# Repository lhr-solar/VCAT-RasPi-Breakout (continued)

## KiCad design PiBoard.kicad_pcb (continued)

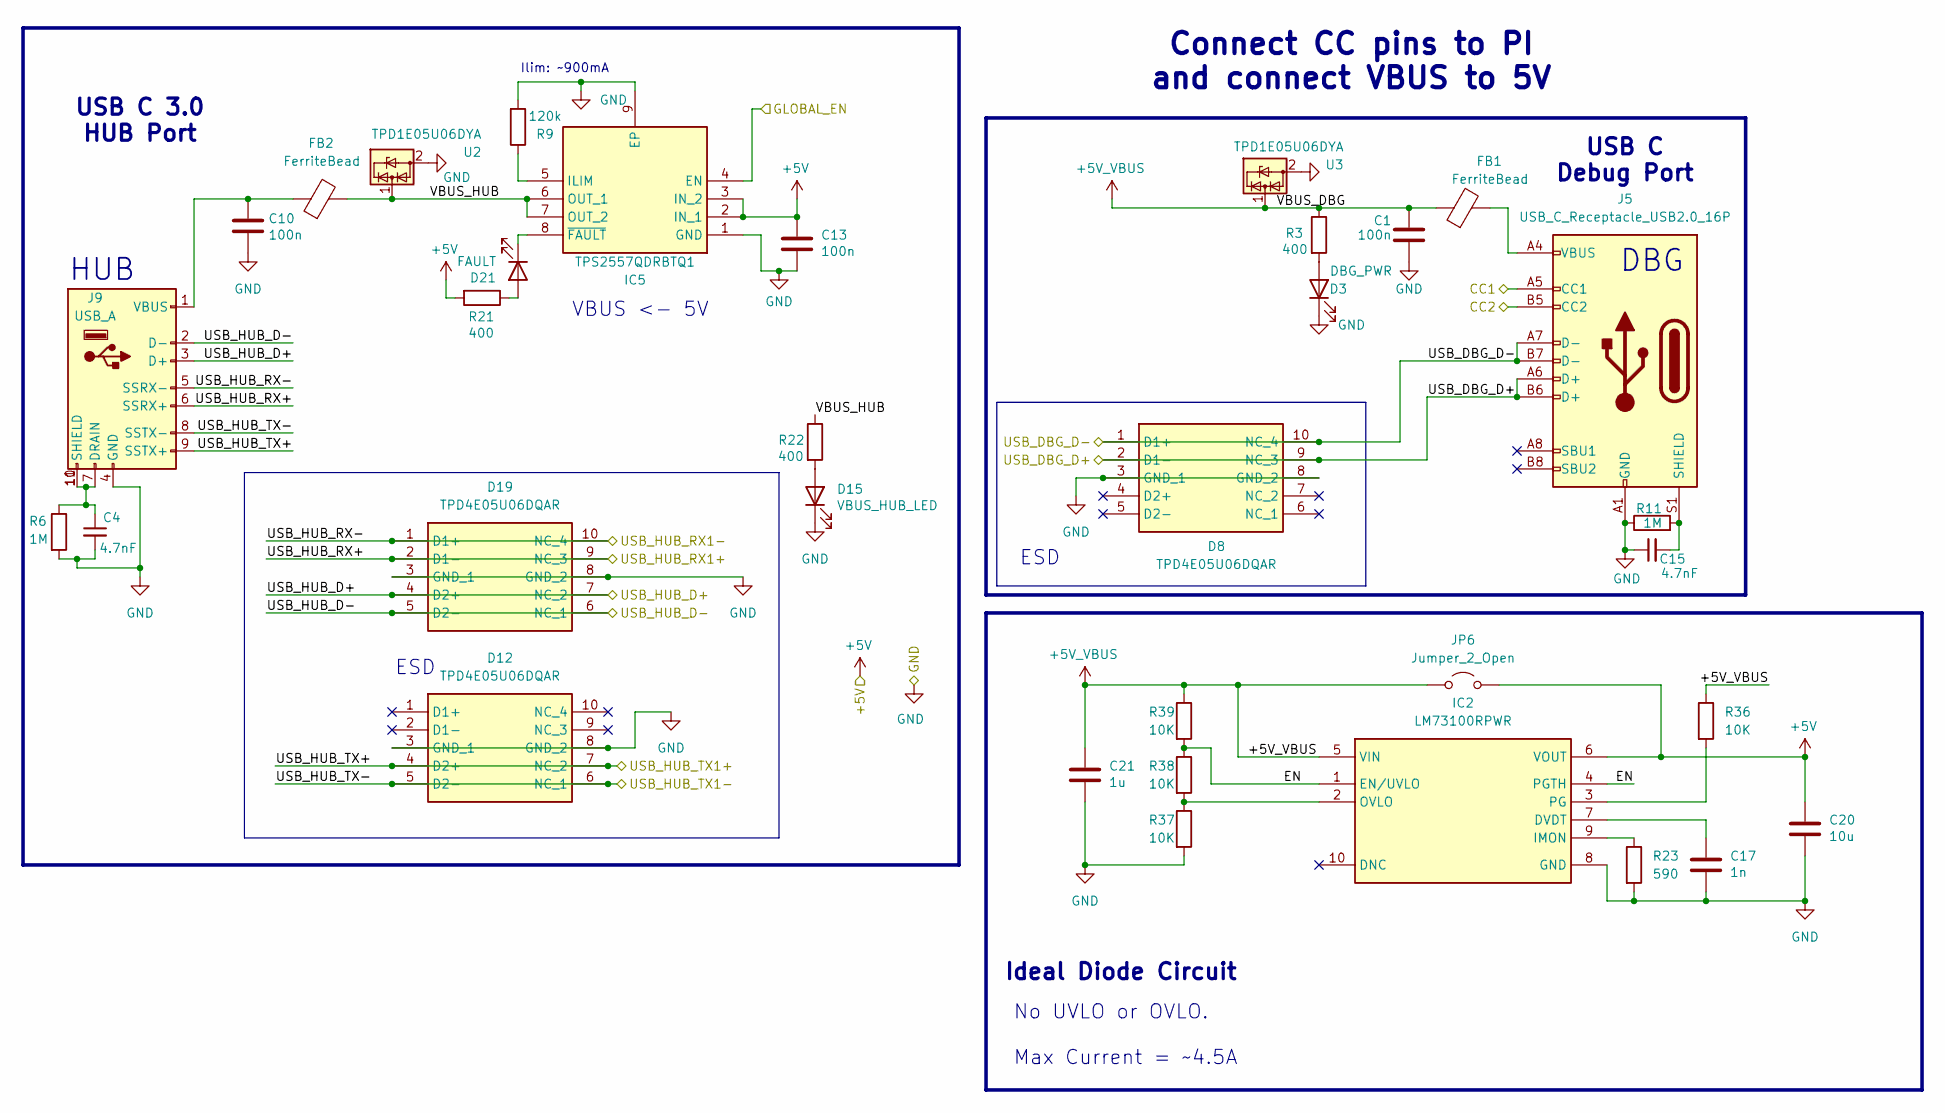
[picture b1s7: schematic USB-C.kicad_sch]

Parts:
C1, C10, C13: 100n; C_0603_1608Metric_Pad1.08x0.95mm_HandSolder; JLC C14663
C4, C15: 4.7nF; C_0603_1608Metric_Pad1.08x0.95mm_HandSolder; JLC C696859
C17: 1n; C_0603_1608Metric_Pad1.08x0.95mm_HandSolder; JLC C1588
C20: 10u; C_0805_2012Metric_Pad1.18x1.45mm_HandSolder; JLC C440198
C21: 1u; C_0603_1608Metric_Pad1.08x0.95mm_HandSolder; JLC C15849
D3: DBG_PWR; LED_0603_1608Metric_Pad1.05x0.95mm_HandSolder; JLC C2289
D8, D12, D19: TPD4E05U06DQAR; IC_TPD4E05U06QDQARQ1; JLC C138714
D15: VBUS_HUB_LED; LED_0603_1608Metric_Pad1.05x0.95mm_HandSolder; JLC C2289
D21: FAULT; LED_0603_1608Metric_Pad1.05x0.95mm_HandSolder; JLC C2286
FB1, FB2: FerriteBead; L_0805_2012Metric_Pad1.05x1.20mm_HandSolder; JLC C1015
IC2: LM73100RPWR; Mouser Part Number 595-LM73100RPWR
IC5: TPS2557QDRBTQ1; SON65P300X300X100-9N-D; Mouser Part Number 595-TPS2557QDRBTQ1
J5: USB_C_Receptacle_USB2.0_16P; USB_C_Receptacle_GCT_USB4105-xx-A_16P_TopMnt_Horizontal; JLC C37616412
J9: USB_A; CONN_484050003_MOL; JLC C565032
JP6: Jumper_2_Open; PinHeader_1x02_P2.54mm_Vertical; JLC N/A
R3, R21, R22: 400; R_0603_1608Metric_Pad0.98x0.95mm_HandSolder; JLC C5841024
R6, R11: 1M; R_0603_1608Metric_Pad0.98x0.95mm_HandSolder; JLC C22935
R9: 120k; R_0603_1608Metric_Pad0.98x0.95mm_HandSolder; JLC C25808
R23: 590; R_0603_1608Metric_Pad0.98x0.95mm_HandSolder; JLC C2076662
R36: 10K; R_0603_1608Metric_Pad0.98x0.95mm_HandSolder; JLC C25804
R37, R38, R39: 10K; R_0603_1608Metric_Pad0.98x0.95mm_HandSolder
U2, U3: TPD1E05U06DYA; D_SOD-523; JLC TPD1E05U06DYAR

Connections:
+5V: C13.1, C20.1, IC2.6 (VOUT), IC5.2 (IN_1), IC5.3 (IN_2), JP6.2 (B), R21.2; also elsewhere on the board
+5V_VBUS: C1.1, C21.1, FB1.1, IC2.5 (VIN), JP6.1 (A), R3.1, R36.1, R39.1, U3.1 (I/O)
/CM5 GPIO/CC1: J5.A5 (CC1); also elsewhere on the board
/CM5 GPIO/CC2: J5.B5 (CC2); also elsewhere on the board
/CM5 GPIO/GLOBAL_EN: IC5.4 (EN); also elsewhere on the board
/High Speed/USB-C/EN: IC2.1 (EN/UVLO), IC2.4 (PGTH), R38.1, R39.2
/High Speed/USB-C/VBUS_HUB: FB2.2, IC5.6 (OUT_1), IC5.7 (OUT_2), R22.1, U2.1 (I/O)
/High Speed/USB_DBG_D+: D8.2 (D1-), D8.9 (NC_3), J5.A6 (D+), J5.B6 (D+); also elsewhere on the board
/High Speed/USB_DBG_D-: D8.1 (D1+), D8.10 (NC_4), J5.A7 (D-), J5.B7 (D-); also elsewhere on the board
/High Speed/USB_HUB_D+: D19.4 (D2+), D19.7 (NC_2), J9.3 (D+); also elsewhere on the board
/High Speed/USB_HUB_D-: D19.5 (D2-), D19.6 (NC_1), J9.2 (D-); also elsewhere on the board
/High Speed/USB_HUB_RX1+: D19.2 (D1-), D19.9 (NC_3), J9.6 (SSRX+); also elsewhere on the board
/High Speed/USB_HUB_RX1-: D19.1 (D1+), D19.10 (NC_4), J9.5 (SSRX-); also elsewhere on the board
/High Speed/USB_HUB_TX1+: D12.4 (D2+), D12.7 (NC_2), J9.9 (SSTX+); also elsewhere on the board
/High Speed/USB_HUB_TX1-: D12.5 (D2-), D12.6 (NC_1), J9.8 (SSTX-); also elsewhere on the board
GND: C1.2, C4.2, C10.2, C13.2, C15.1, C17.2, C20.2, C21.2, D3.1 (K), D8.3 (GND_1), D8.8 (GND_2), D12.3 (GND_1), D12.8 (GND_2), D15.1 (K), D19.3 (GND_1), D19.8 (GND_2), IC2.8 (GND), IC5.1 (GND), IC5.9 (EP), J5.A1 (GND), J5.A12 (GND), J5.B1 (GND), J5.B12 (GND), J9.4 (GND), R6.2, R9.2, R11.1, R23.2, R37.2, U2.2 (GND), U3.2 (GND); also elsewhere on the board
unnamed: D3.2 (A), R3.2
unnamed: D15.2 (A), R22.2
unnamed: D21.2 (A), R21.1
unnamed: D21.1 (K), IC5.8 (~FAULT)
unnamed: FB1.2, J5.A4 (VBUS), J5.A9 (VBUS), J5.B4 (VBUS), J5.B9 (VBUS)
unnamed: C17.1, IC2.7 (DVDT)
unnamed: IC2.9 (IMON), R23.1
unnamed: IC2.2 (OVLO), R37.1, R38.2
unnamed: IC2.3 (PG), R36.2
unnamed: IC5.5 (ILIM), R9.1
unnamed: C15.2, J5.S1 (SHIELD), R11.2
unnamed: C4.1, J9.7 (DRAIN), J9.10 (SHIELD), J9.11 (SHIELD), R6.1
unnamed: C10.1, FB2.1, J9.1 (VBUS)

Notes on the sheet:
Ideal Diode Circuit
Ilim: ~900mA
DBG
ESD
No UVLO or OVLO. Max Current = ~4.5A
HUB
Connect CC pins to PI and connect VBUS to 5V
VBUS <- 5V
USB C 3.0 HUB Port
USB C Debug Port

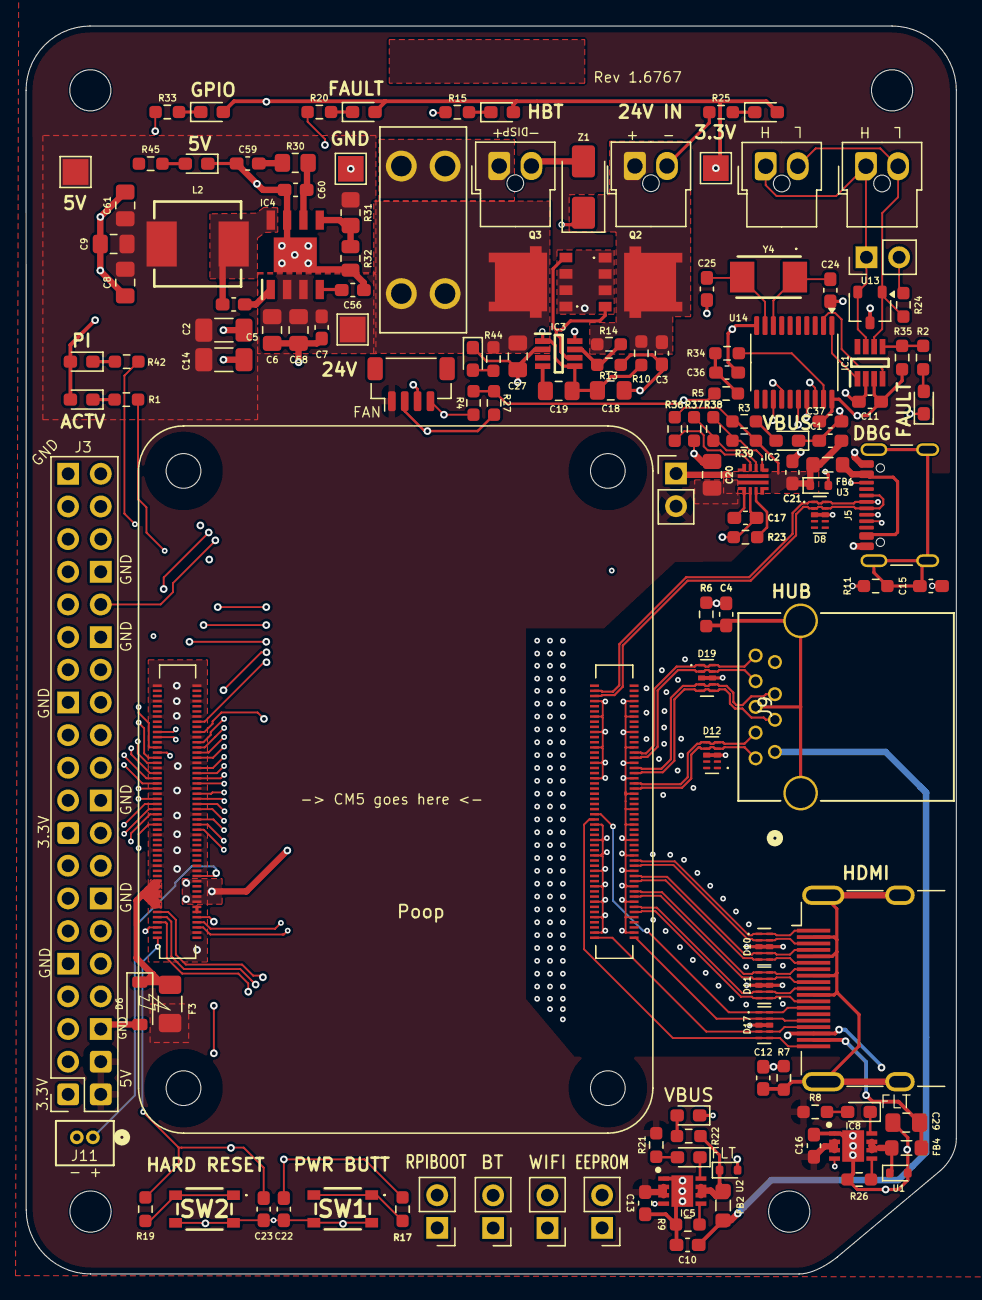
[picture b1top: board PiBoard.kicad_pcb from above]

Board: 4 copper layers, 72.3 x 97.1 mm, 139 parts (0 on the bottom side), 123 nets.

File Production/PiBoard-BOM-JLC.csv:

"Reference","Value","Footprint","Qty","JLC"
"U1,U2,U3","TPD1E05U06DYA","Diode_SMD:D_SOD-523","3","TPD1E05U06DYAR"
"BT2,H1,H2,H3,H4,IC3,J1,J2,J3,J6,J8,J11,J12,J14,JP1,JP2,JP3,JP4,JP5,JP6,TP1,TP2,TP3,TP5","Battery_Cell,CarCANConnector,CarLVPowerConnector,Display Breakout,Fan Header,Jumper_2_Open,LM74502HDDFR,MountingHole,RPI Pin-Header,RTC Battery Conn,RTC Battery Port,TestPoint","Connector_JST:JST_SH_BM04B-SRSS-TB_1x04-1MP_P1.00mm_Vertical,Connector_PinHeader_2.54mm:PinHeader_1x02_P2.54mm_Vertical,Connector_PinSocket_2.54mm:PinSocket_2x20_P2.54mm_Vertical,Controls_Pi:CONN02_530470210_MOL,MountingHole:MountingHole_3.2mm_M3,TestPoint:TestPoint_Pad_2.0x2.0mm,UTSVT_Connectors:Molex_Nano-Fit_105309-xx02_1x02_P2.50mm_Vertical,UTSVT_Power_SP:SOT65P280X110-8N","24","N/A"
"Q2,Q3","NVMFWS1D7N04XMT1G","Controls_Pi:NVMFWS3D0P04M8LT1G","2","C52190853"
"F3","RFuse","Fuse:Fuse_1206_3216Metric_Pad1.42x1.75mm_HandSolder","1","C42449089"
"J5","USB_C_Receptacle_USB2.0_16P","UTSVT_Connectors:USB_C_Receptacle_GCT_USB4105-xx-A_16P_TopMnt_Horizontal","1","C37616412"
"R26","180k","Resistor_SMD:R_0603_1608Metric_Pad0.98x0.95mm_HandSolder","1","C22356446"
"D6","PTVS6V0S1UR","Diode_SMD:D_SOD-123","1"," C18723426"
"C2,C14","100uF","Capacitor_SMD:C_1206_3216Metric_Pad1.33x1.80mm_HandSolder","2","C7432784"
"Z1","SMAF4759A-TP","Diode_SMD:D_SMA","1","C7083101"
"Module2","ComputeModule5-CM5","CM5IO:Raspberry-Pi-5-Compute-Module","1","C6782225"
"R3,R8,R21,R22,R45","400","Resistor_SMD:R_0603_1608Metric_Pad0.98x0.95mm_HandSolder","5","C5841024"
"L2","4.7uH","Controls_Pi:INDPM110100X540N","1","C5189748"
"U13","CDSOT23-T24CAN","Package_TO_SOT_SMD:SOT-23W","1","C2959841"
"R31","53.6k","Resistor_SMD:R_0805_2012Metric_Pad1.20x1.40mm_HandSolder","1","C2930115"
"SW1,SW2","SW_Push","CM5IO:TL3365AF180QG","2","C2886926"
"IC5,IC8","TPS2557QDRBTQ1","Controls_Pi:SON65P300X300X100-9N-D","2","C2149775"
"IC4","AP64501QSP-13","Controls_Pi:SOIC127P600X163-9N","1","C2071517"
"J7","HDMI_A_1.4","Connector_Video:HDMI_A_Molex_208658-1001_Horizontal","1","C916313"
"C4,C12,C15","4.7nF","Capacitor_SMD:C_0603_1608Metric_Pad1.08x0.95mm_HandSolder","3","C696859"
"U14","MCP2515T-E/ST","Package_SO:TSSOP-20_4.4x6.5mm_P0.65mm","1","C627064"
"J9","USB_A","Controls_Pi:CONN_484050003_MOL","1","C565032"
"R44","3k","Resistor_SMD:R_0603_1608Metric_Pad0.98x0.95mm_HandSolder","1","C445829"
"C6,C27,C58","10uF","Capacitor_SMD:C_0805_2012Metric_Pad1.18x1.45mm_HandSolder","3","C440198"
"C8,C9,C61","22uF","Capacitor_SMD:C_0805_2012Metric_Pad1.18x1.45mm_HandSolder","3","C338078"
"Y4","8 MHz","Controls_Pi:ABM3","1","C144380"
"D8,D10,D11,D12,D17,D19","TPD4E05U06DQAR","Controls_Pi:IC_TPD4E05U06QDQARQ1","6","C138714"
"IC1","TCAN337DCNR","Controls_Pi:SOT65P280X145-8N","1","C130129"
"C59","2.7nF","Capacitor_SMD:C_0603_1608Metric_Pad1.08x0.95mm_HandSolder","1","C107085"
"C18","1uF","Capacitor_SMD:C_0805_2012Metric_Pad1.18x1.45mm_HandSolder","1","C28323"
"R14","200k","Resistor_SMD:R_0603_1608Metric_Pad0.98x0.95mm_HandSolder","1","C25811"
"R9","120k","Resistor_SMD:R_0603_1608Metric_Pad0.98x0.95mm_HandSolder","1","C25808"
"R4,R10,R13,R27,R34,R35","10k","Resistor_SMD:R_0603_1608Metric_Pad0.98x0.95mm_HandSolder","6","C25804"
"R6,R7,R11","1M","Resistor_SMD:R_0603_1608Metric_Pad0.98x0.95mm_HandSolder","3","C22935"
"R24","120","Resistor_SMD:R_0603_1608Metric_Pad0.98x0.95mm_HandSolder","1","C22787"
"R1,R2,R15,R20,R25,R33,R42","100","Resistor_SMD:R_0603_1608Metric_Pad0.98x0.95mm_HandSolder","7","C22775"
"R5,R17,R19","1k","Resistor_SMD:R_0603_1608Metric_Pad0.98x0.95mm_HandSolder","3","C21190"
"C19","220nF","Capacitor_SMD:C_0805_2012Metric_Pad1.18x1.45mm_HandSolder","1","C21120"
"R30","15.8k","Resistor_SMD:R_0805_2012Metric_Pad1.20x1.40mm_HandSolder","1","C17468"
"R32","10k","Resistor_SMD:R_0805_2012Metric","1","C17414"
"C29","47uF","Capacitor_SMD:C_0805_2012Metric_Pad1.18x1.45mm_HandSolder","1","C16780"
"C1,C3,C5,C7,C10,C11,C13,C16,C22,C23,C36,C37","100n","Capacitor_SMD:C_0603_1608Metric_Pad1.08x0.95mm_HandSolder","12","C14663"
"D1,D2,D3,D5,D7,D9,D13,D15,D16","24V PWR LED,3.3V PWR,5V PWR LED,Activity,DBG_PWR,HBT,PI PWR,STUFF,VBUS_HUB_LED","LED_SMD:LED_0603_1608Metric_Pad1.05x0.95mm_HandSolder","9","C2289"
"D4,D14,D18,D21","CAN Fault LED,FAULT","LED_SMD:LED_0603_1608Metric_Pad1.05x0.95mm_HandSolder","4","C2286"
"C60","33pF","Capacitor_SMD:C_0603_1608Metric_Pad1.08x0.95mm_HandSolder","1","C1663"
"C24,C25","22 pF","Capacitor_SMD:C_0603_1608Metric_Pad1.08x0.95mm_HandSolder","2","C1653"
"C56","10nF","Capacitor_SMD:C_0603_1608Metric_Pad1.08x0.95mm_HandSolder","1","C1589"
"FB1,FB2,FB4","FerriteBead","Inductor_SMD:L_0805_2012Metric_Pad1.05x1.20mm_HandSolder","3","C1015"
"F1","3568","Controls_Pi:FUSE_3568","1",""

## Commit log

2025-01-17 think im done with schematic
2025-01-17 removed kicad session objects
2025-01-25 small changes for ravi
2025-01-25 silly mistake
2025-02-01 some stuff
2025-02-16 added parts to almost everything (except can xtal and fuses)
2025-02-26 fixed cap sizes, added remaining parts, fixed rtc battery
2025-03-01 review committee changes implmented
2025-03-02 fixed relevant erc errors
2025-04-02 layout 1.0 kinda done
2025-04-12 more compact
2025-06-14 small notes
2025-06-22 added 3d models
2025-06-23 moved some stuff around
2025-06-27 Migrate to USB C and added some ESD protections on Vbus; might still have some issues
2025-06-28 fixed erc and removed old schematics
2025-07-14 updated power to 24V i think
2025-08-04 changed usb to be simpler (no inbuilt hub)
2025-08-11 layout draft
2025-08-16 moved everything to front & 0603'd stuff
2025-08-18 mostly routed, except highspeed
2025-08-25 added new power, but lowkey need to redo a bunch of shit
2025-08-26 ready to route high speed i believe
2025-08-30 changed a bunch of stuff, still have work
2025-09-13 fart
2025-09-19 poop
2025-09-20 my life is horrible
2025-10-04 moved things to their own sheets
2025-10-04 rrrrrrrr
2025-10-04 add new lib frfr
2025-10-04 Schem done? [plz full review], redoing layout
2025-10-11 I hate my life
2025-10-17 I'm unhappy with the state of the world
2025-10-25 frank
2025-10-25 frank2
2025-10-25 Copy of I hate my life pt2.5 final final (3)
2025-10-29 wow everything could not be worse
2025-10-30 my life could not be worse right now
2025-11-01 frink
2025-11-01 frink2
2025-11-01 I plead that my suffering is nearing its end
2025-11-01 frink4
2025-11-08 chang
2025-11-15 fjfdsfdslk
2025-11-15 P/Ns
2025-11-22 silkscreens
2025-11-22 silkscreen n shit
2025-11-22 jlc shit
2025-12-05 mostly fixed alignment
2025-12-06 ravi
2025-12-06 stupid git
2025-12-07 fixed
2025-12-07 fixed again
2026-01-18 Rev A (#1)
    * updated readme
    * small changes for ravi
    * silly mistake
    * some stuff
    * added parts to almost everything (except can xtal and fuses)
    * fixed cap sizes, added remaining parts, fixed rtc battery
2026-02-03 ideal diode circuit protection on usbc
2026-02-04 addressing mika's comments
2026-02-04 mika changes
2026-02-14 mika fixes
2026-06-18 Mika (#2)
    * poop
    * poop
    * poop
    * poop
    * poop
    * ideal diode circuit protection on usbc
